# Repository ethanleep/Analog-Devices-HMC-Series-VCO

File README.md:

# Analog Devices HMC Series VCO

These are the board files for a VCO on the Analog Devices HMC series VCO ICs. These are a wide range of high frequency inexpensive VCOs that can generate frequencies up to 8GHz. This board should work up to the HMC506 chip. It has tested and verified to work but I cannot guarantee performance characteristics because I simply dont have the tools to test it. The boards are 4 layer FR408 PCBs ordered from OSH Park due to the decent RF performance and cost. The SMA footprints on the board are based off of Molex connectors but they work fine with other brands even if the sizes dont match. The boards are uploaded to the OSH Park website and can be viewed and ordered below.

HMC Series VCOs: https://www.analog.com/en/products/rf-microwave/vcos-plos/vcos-with-single-output.html

OSH Park PCB link: <a href="https://oshpark.com/shared_projects/ALN9admB"></img></a>

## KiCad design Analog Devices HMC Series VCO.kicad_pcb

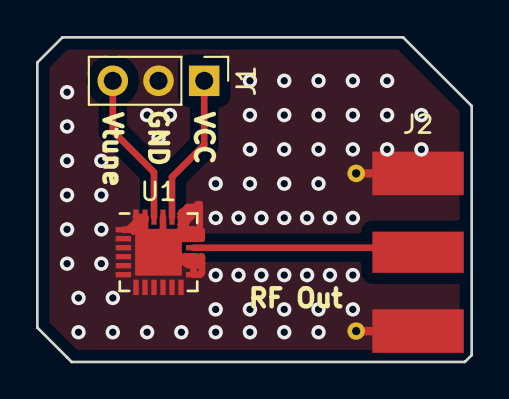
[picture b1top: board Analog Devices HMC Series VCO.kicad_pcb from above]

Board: 4 copper layers, 24.1 x 18.0 mm, 3 parts (0 on the bottom side), 4 nets.

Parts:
J1: Conn_01x03_Male; Socket_Strip_Straight_1x03_Pitch2.54mm
J2: Conn_Coaxial; Molex_SMA_Jack_Edge_Mount
U1: HMC431; QFN-24-1EP_4x4mm_Pitch0.5mm

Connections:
unnamed: J1.1, U1.20
unnamed: J1.2, J2.2, U1.1, U1.2, U1.3, U1.4, U1.5, U1.6, U1.7, U1.8, U1.9, U1.10, U1.11, U1.12, U1.13, U1.14, U1.15, U1.17, U1.18, U1.19, U1.21, U1.23, U1.24, U1.25
unnamed: J1.3, U1.22
unnamed: J2.1, U1.16

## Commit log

2019-05-25 Added Board Files
2019-05-25 Updated Board files
